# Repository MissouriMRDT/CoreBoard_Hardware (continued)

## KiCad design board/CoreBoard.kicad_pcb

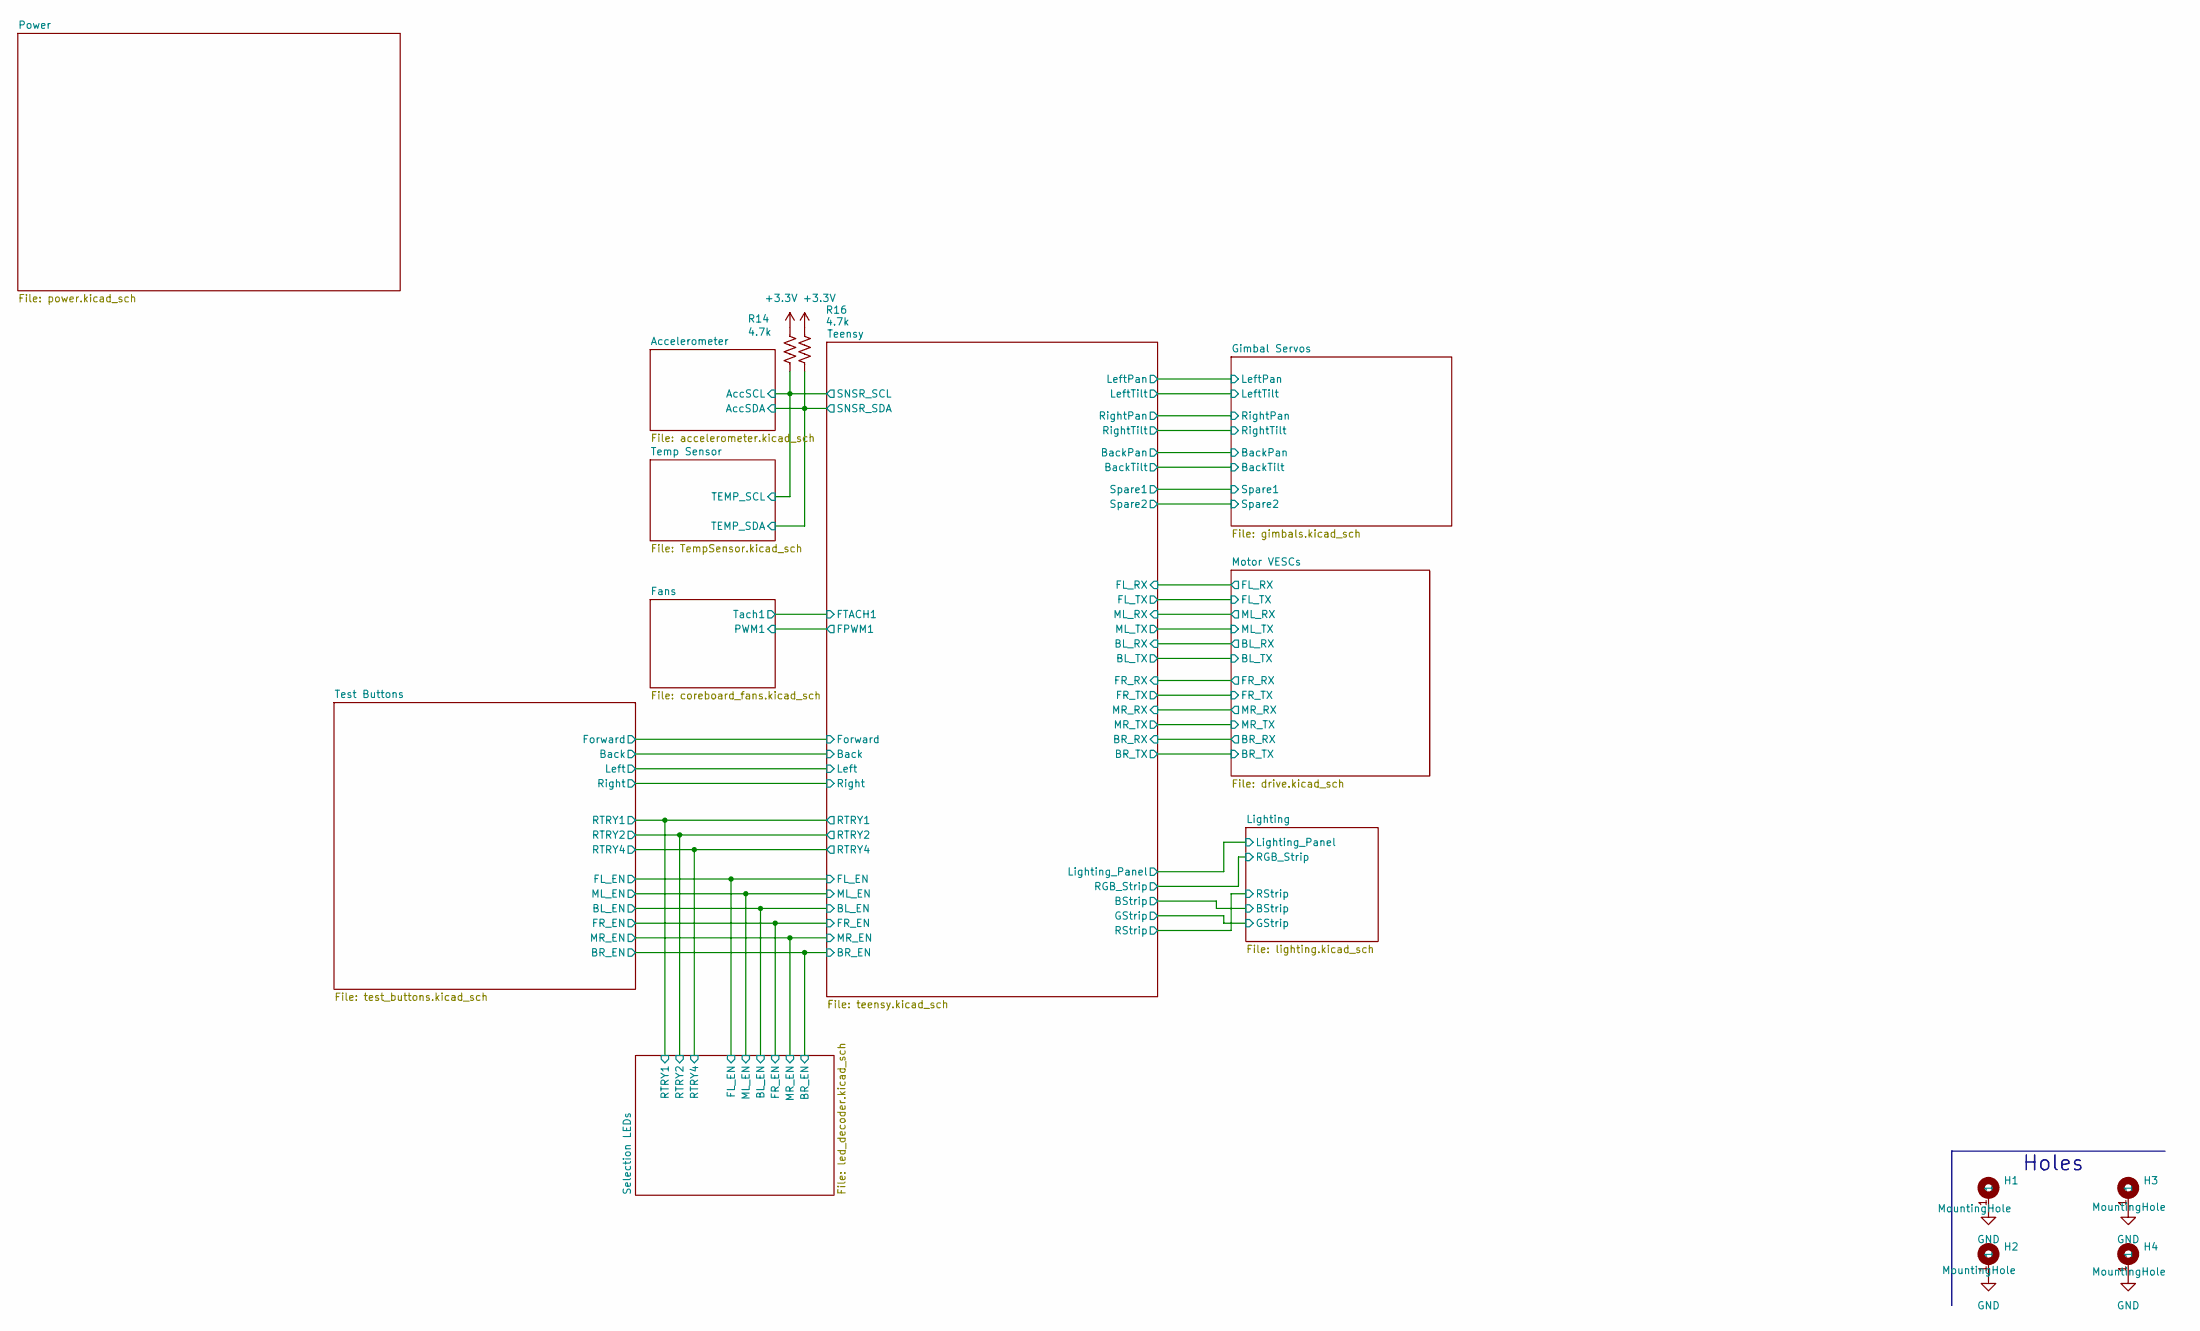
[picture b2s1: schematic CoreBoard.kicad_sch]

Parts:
H1, H2, H3, H4: MountingHole; 4_40_Hole_Pad_Via
R14, R16: 4.7k; R_0603_1608Metric_Pad0.98x0.95mm_HandSolder

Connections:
+3.3V: R14.1, R16.1; also elsewhere on the board
/Accelerometer/AccSCL: R14.2; also elsewhere on the board
/Accelerometer/AccSDA: R16.2; also elsewhere on the board
GND: H1.1, H2.1, H3.1, H4.1; also elsewhere on the board

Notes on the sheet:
Holes

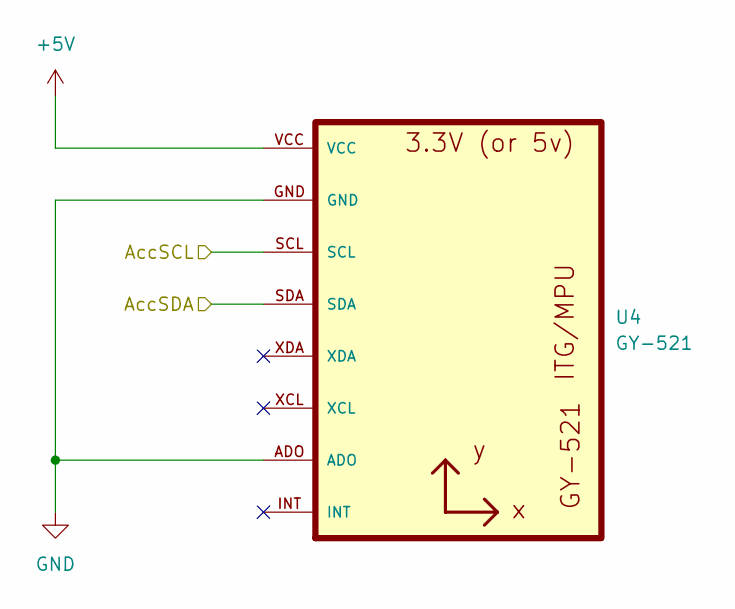
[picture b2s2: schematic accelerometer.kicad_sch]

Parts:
U4: GY-521

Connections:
+5V: U4.VCC; also elsewhere on the board
/Accelerometer/AccSCL: U4.SCL; also elsewhere on the board
/Accelerometer/AccSDA: U4.SDA; also elsewhere on the board
GND: U4.ADO, U4.GND; also elsewhere on the board

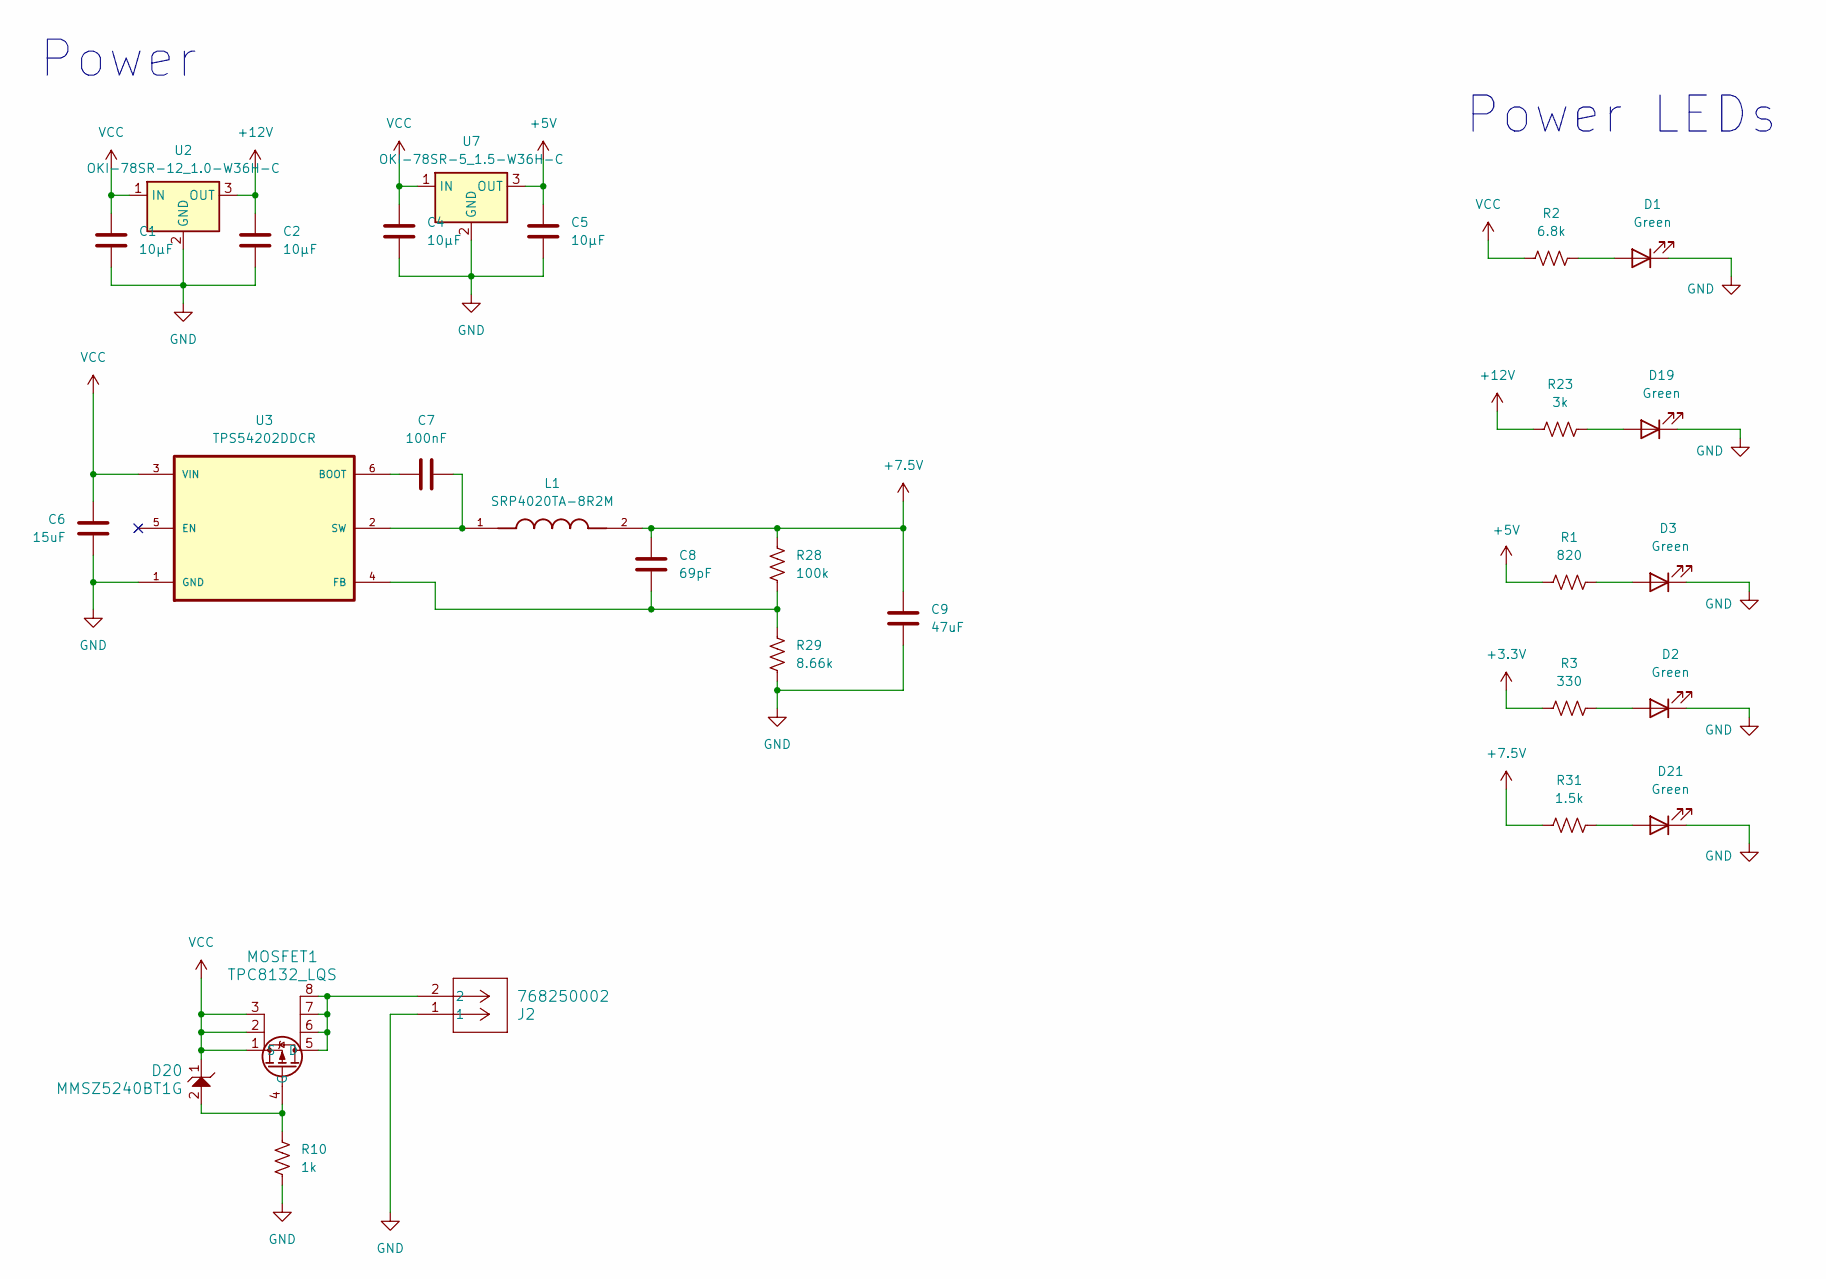
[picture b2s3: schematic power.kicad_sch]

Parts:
C1, C4: 10µF; C_1206_3216Metric_Pad1.33x1.80mm_HandSolder
C2, C5: 10µF; C_0603_1608Metric_Pad1.08x0.95mm_HandSolder
C6: 15uF; C_0805_2012Metric_Pad1.18x1.45mm_HandSolder
C7: 100nF; C_0603_1608Metric
C8: 69pF; C_0603_1608Metric
C9: 47uF; C_1206_3216Metric
D1, D2, D3, D19, D21: Green; LED_0603_1608Metric_Pad1.05x0.95mm_HandSolder
D20: MMSZ5240BT1G; SOD-123_ONS-L
J2: 768250002; MOLEX_MegaFit_02_Horizontal
L1: SRP4020TA-8R2M; IND_SRP4020TA-8R2M
MOSFET1: TPC8132_LQS; SOIC-8_3.9x4.9mm_P1.27mm
R1: 820; R_0603_1608Metric_Pad0.98x0.95mm_HandSolder
R2: 6.8k; R_0603_1608Metric_Pad0.98x0.95mm_HandSolder
R3: 330; R_0603_1608Metric_Pad0.98x0.95mm_HandSolder
R10: 1k; R_0603_1608Metric_Pad0.98x0.95mm_HandSolder
R23: 3k; R_0603_1608Metric_Pad0.98x0.95mm_HandSolder
R28: 100k; R_0603_1608Metric
R29: 8.66k; R_0603_1608Metric
R31: 1.5k; R_0603_1608Metric_Pad0.98x0.95mm_HandSolder
U2: OKI-78SR-12_1.0-W36H-C; Converter_DCDC_Murata_OKI-78SR_Horizontal
U3: TPS54202DDCR; SOT95P280X110-6N; MPN TPS54202DDCR
U7: OKI-78SR-5_1.5-W36H-C; Converter_DCDC_Murata_OKI-78SR_Horizontal

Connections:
+3.3V: R3.1; also elsewhere on the board
+5V: C5.1, R1.1, U7.3 (OUT); also elsewhere on the board
+7.5V: C8.1, C9.1, L1.2, R28.1, R31.1; also elsewhere on the board
+12V: C2.1, R23.1, U2.3 (OUT); also elsewhere on the board
GND: C1.2, C2.2, C4.2, C5.2, C6.2, C9.2, D1.1 (K), D2.1 (K), D3.1 (K), D19.1 (K), D21.1 (K), J2.1, R10.1, R29.2, U2.2 (GND), U3.1 (GND), U7.2 (GND); also elsewhere on the board
unnamed: D1.2 (A), R2.2
unnamed: D2.2 (A), R3.2
unnamed: D3.2 (A), R1.2
unnamed: D19.2 (A), R23.2
unnamed: D21.2 (A), R31.2
unnamed: J2.2, MOSFET1.5 (D), MOSFET1.6, MOSFET1.7, MOSFET1.8
unnamed: D20.2, MOSFET1.4 (G), R10.2
unnamed: C7.1, U3.6 (BOOT)
unnamed: C8.2, R28.2, R29.1, U3.4 (FB)
unnamed: C7.2, L1.1, U3.2 (SW)
VCC: C1.1, C4.1, C6.1, D20.1, MOSFET1.1 (S), MOSFET1.2, MOSFET1.3, R2.1, U2.1 (IN), U3.3 (VIN), U7.1 (IN)

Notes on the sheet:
Power
Power LEDs

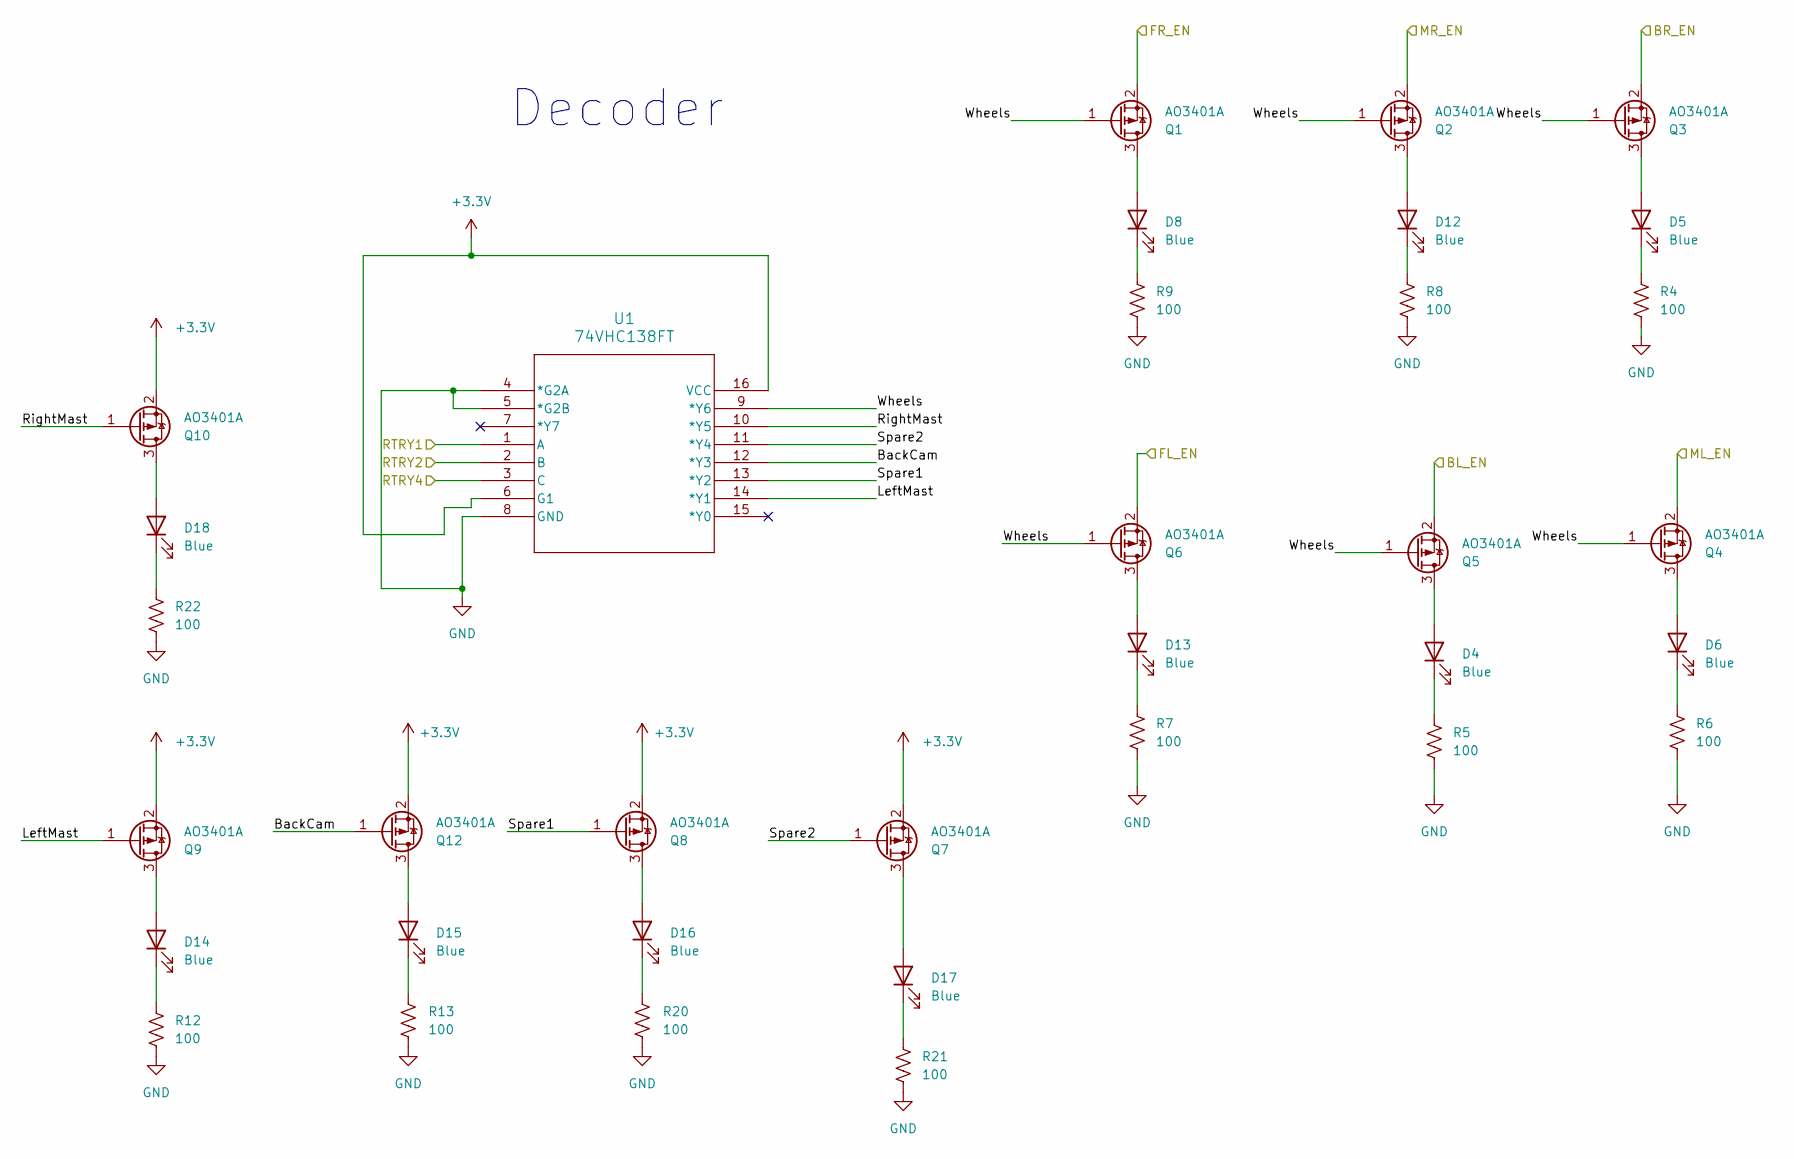
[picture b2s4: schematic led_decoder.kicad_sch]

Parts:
D4, D5, D6, D8, D12, D13, D14, D15, D16, D17, D18: Blue; LED_0603_1608Metric_Pad1.05x0.95mm_HandSolder
Q1, Q2, Q3, Q4, Q5, Q6, Q7, Q8, Q9, Q10, Q12: AO3401A; SOT-23
R4, R5, R6, R7, R8, R9, R12, R13, R20, R21, R22: 100; R_0603_1608Metric_Pad0.98x0.95mm_HandSolder
U1: 74VHC138FT; TSSOP16B_TOS-L

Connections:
+3.3V: Q7.2 (S), Q8.2 (S), Q9.2 (S), Q10.2 (S), Q12.2 (S), U1.6 (G1), U1.16 (VCC); also elsewhere on the board
/Selection LEDs/BL_EN: Q5.2 (S); also elsewhere on the board
/Selection LEDs/BR_EN: Q3.2 (S); also elsewhere on the board
/Selection LEDs/BackCam: Q12.1 (G), U1.12 (*Y3)
/Selection LEDs/FL_EN: Q6.2 (S); also elsewhere on the board
/Selection LEDs/FR_EN: Q1.2 (S); also elsewhere on the board
/Selection LEDs/LeftMast: Q9.1 (G), U1.14 (*Y1)
/Selection LEDs/ML_EN: Q4.2 (S); also elsewhere on the board
/Selection LEDs/MR_EN: Q2.2 (S); also elsewhere on the board
/Selection LEDs/RTRY1: U1.1 (A); also elsewhere on the board
/Selection LEDs/RTRY2: U1.2 (B); also elsewhere on the board
/Selection LEDs/RTRY4: U1.3 (C); also elsewhere on the board
/Selection LEDs/RightMast: Q10.1 (G), U1.10 (*Y5)
/Selection LEDs/Spare1: Q8.1 (G), U1.13 (*Y2)
/Selection LEDs/Spare2: Q7.1 (G), U1.11 (*Y4)
/Selection LEDs/Wheels: Q1.1 (G), Q2.1 (G), Q3.1 (G), Q4.1 (G), Q5.1 (G), Q6.1 (G), U1.9 (*Y6)
GND: R4.1, R5.1, R6.1, R7.1, R8.1, R9.1, R12.1, R13.1, R20.1, R21.1, R22.1, U1.4 (*G2A), U1.5 (*G2B), U1.8 (GND); also elsewhere on the board
unnamed: D4.2 (A), Q5.3 (D)
unnamed: D4.1 (K), R5.2
unnamed: D5.2 (A), Q3.3 (D)
unnamed: D5.1 (K), R4.2
unnamed: D6.2 (A), Q4.3 (D)
unnamed: D6.1 (K), R6.2
unnamed: D8.2 (A), Q1.3 (D)
unnamed: D8.1 (K), R9.2
unnamed: D12.2 (A), Q2.3 (D)
unnamed: D12.1 (K), R8.2
unnamed: D13.2 (A), Q6.3 (D)
unnamed: D13.1 (K), R7.2
unnamed: D14.2 (A), Q9.3 (D)
unnamed: D14.1 (K), R12.2
unnamed: D15.2 (A), Q12.3 (D)
unnamed: D15.1 (K), R13.2
unnamed: D16.2 (A), Q8.3 (D)
unnamed: D16.1 (K), R20.2
unnamed: D17.2 (A), Q7.3 (D)
unnamed: D17.1 (K), R21.2
unnamed: D18.2 (A), Q10.3 (D)
unnamed: D18.1 (K), R22.2

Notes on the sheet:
Decoder

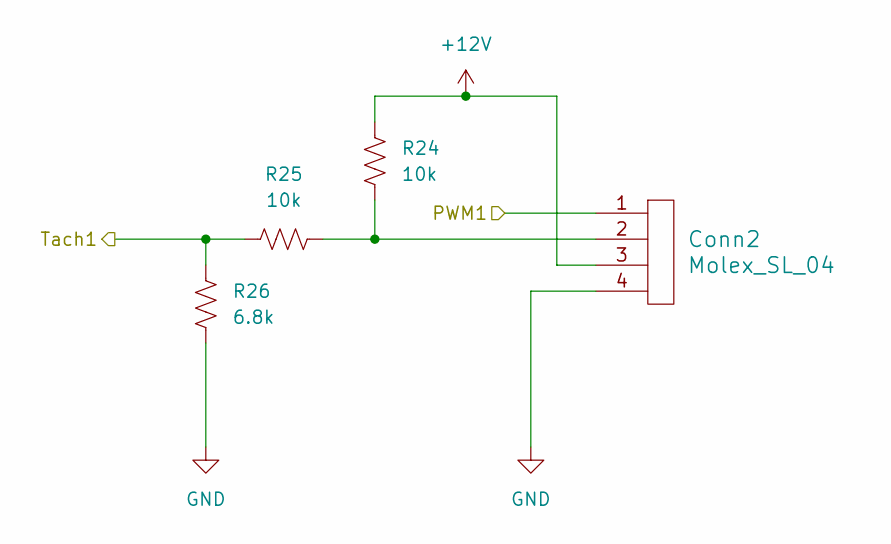
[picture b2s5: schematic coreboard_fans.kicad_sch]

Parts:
Conn2: Molex_SL_04; MOLEX_SL_04_Horizontal
R24, R25: 10k; R_0603_1608Metric_Pad0.98x0.95mm_HandSolder
R26: 6.8k; R_0603_1608Metric_Pad0.98x0.95mm_HandSolder

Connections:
+12V: Conn2.3, R24.1; also elsewhere on the board
/Fans/PWM1: Conn2.1; also elsewhere on the board
/Fans/Tach1: R25.2, R26.1; also elsewhere on the board
GND: Conn2.4, R26.2; also elsewhere on the board
unnamed: Conn2.2, R24.2, R25.1

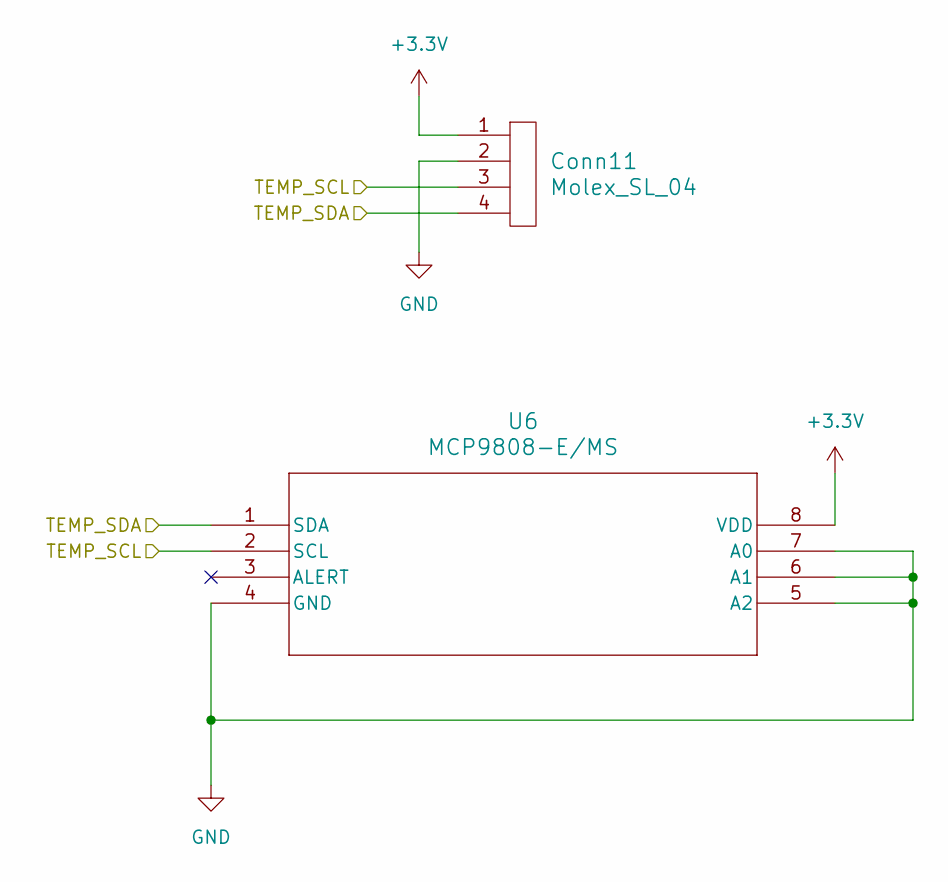
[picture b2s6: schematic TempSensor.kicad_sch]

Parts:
Conn11: Molex_SL_04; MOLEX_SL_04_Vertical
U6: MCP9808-E/MS; MSOP8_MC_MCH-L

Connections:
+3.3V: Conn11.1, U6.8 (VDD); also elsewhere on the board
/Accelerometer/AccSCL: Conn11.3, U6.2 (SCL); also elsewhere on the board
/Accelerometer/AccSDA: Conn11.4, U6.1 (SDA); also elsewhere on the board
GND: Conn11.2, U6.4 (GND), U6.5 (A2), U6.6 (A1), U6.7 (A0); also elsewhere on the board

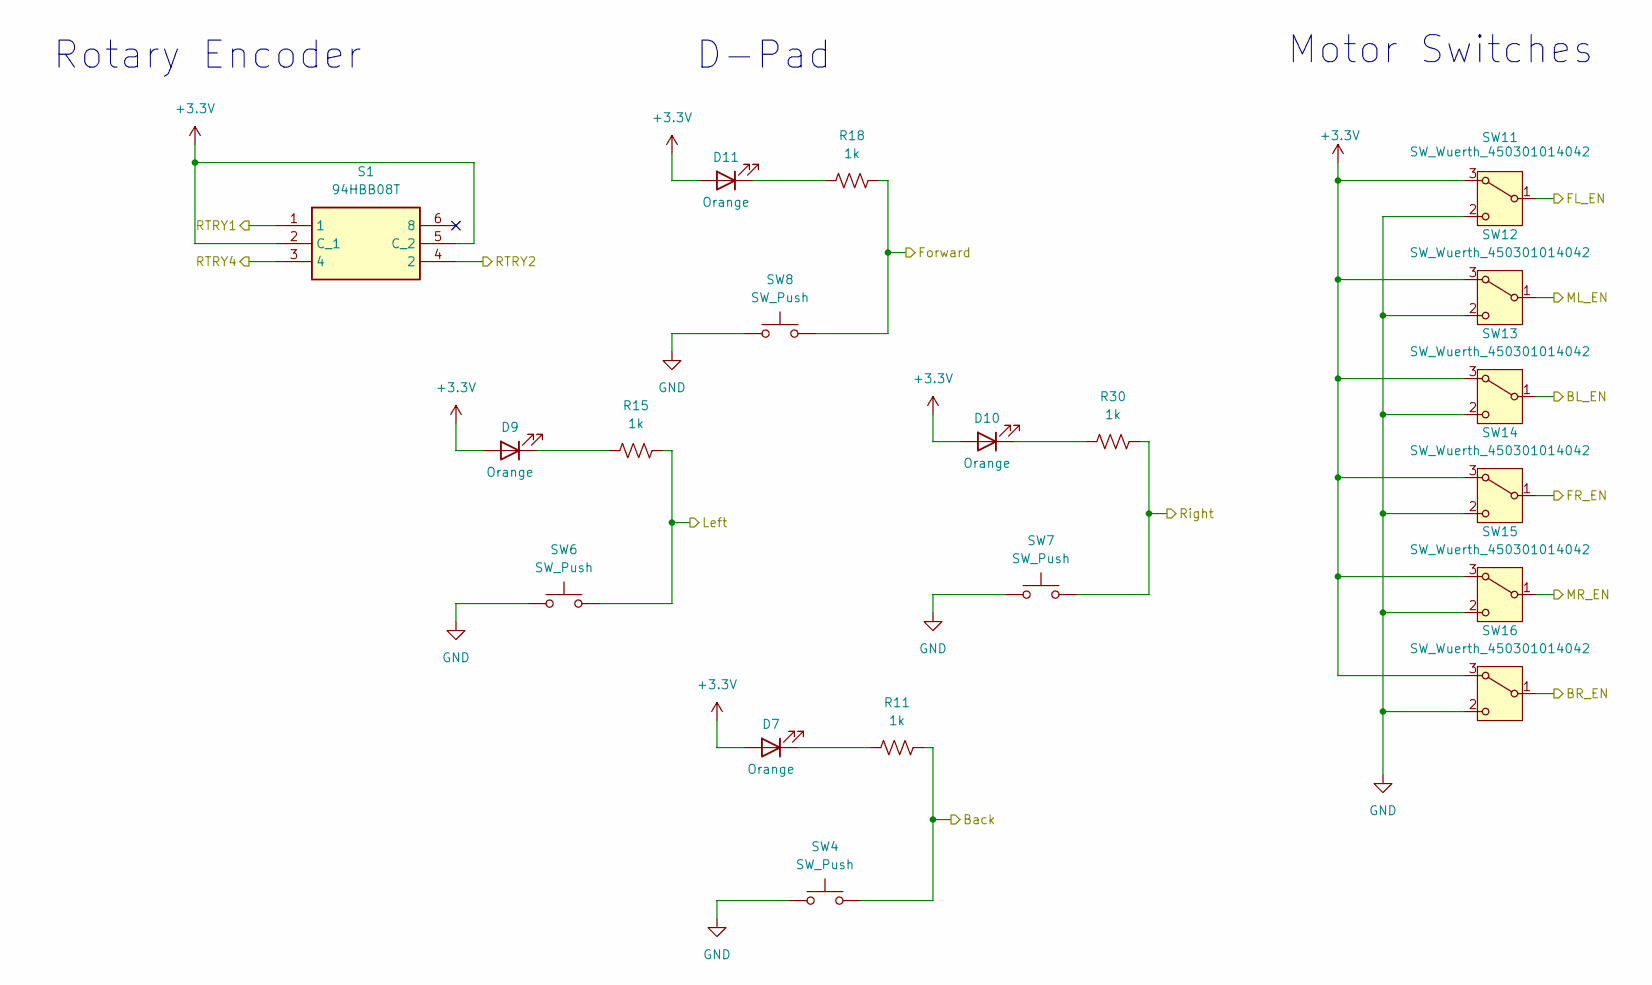
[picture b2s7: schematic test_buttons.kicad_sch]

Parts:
D7, D9, D10, D11: Orange; LED_0603_1608Metric_Pad1.05x0.95mm_HandSolder
R11, R15, R18, R30: 1k; R_0603_1608Metric_Pad0.98x0.95mm_HandSolder
S1: 94HBB08T; DIPS762W56P254L991H597Q6N; Manufacturer_Part_Number 94HBB08T; Mouser Part Number 706-94HBB08T
SW4, SW6, SW7, SW8: SW_Push; SW_SPST_TL3305A
SW11, SW12, SW13, SW14, SW15, SW16: SW_Wuerth_450301014042; SW_Slide-03_Wuerth-WS-SLTV_10x2.5x6.4_P2.54mm

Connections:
+3.3V: D7.2 (A), D9.2 (A), D10.2 (A), D11.2 (A), S1.2 (C_1), S1.5 (C_2), SW11.3 (A), SW12.3 (A), SW13.3 (A), SW14.3 (A), SW15.3 (A), SW16.3 (A); also elsewhere on the board
/Selection LEDs/BL_EN: SW13.1 (B); also elsewhere on the board
/Selection LEDs/BR_EN: SW16.1 (B); also elsewhere on the board
/Selection LEDs/FL_EN: SW11.1 (B); also elsewhere on the board
/Selection LEDs/FR_EN: SW14.1 (B); also elsewhere on the board
/Selection LEDs/ML_EN: SW12.1 (B); also elsewhere on the board
/Selection LEDs/MR_EN: SW15.1 (B); also elsewhere on the board
/Selection LEDs/RTRY1: S1.1; also elsewhere on the board
/Selection LEDs/RTRY2: S1.4 (2); also elsewhere on the board
/Selection LEDs/RTRY4: S1.3 (4); also elsewhere on the board
/Teensy/Back: R11.1, SW4.2; also elsewhere on the board
/Teensy/Forward: R18.1, SW8.2; also elsewhere on the board
/Teensy/Left: R15.1, SW6.2; also elsewhere on the board
/Teensy/Right: R30.1, SW7.2; also elsewhere on the board
GND: SW4.1, SW6.1, SW7.1, SW8.1, SW11.2 (C), SW12.2 (C), SW13.2 (C), SW14.2 (C), SW15.2 (C), SW16.2 (C); also elsewhere on the board
unnamed: D7.1 (K), R11.2
unnamed: D9.1 (K), R15.2
unnamed: D10.1 (K), R30.2
unnamed: D11.1 (K), R18.2

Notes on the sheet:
Motor Switches
Rotary Encoder
D-Pad

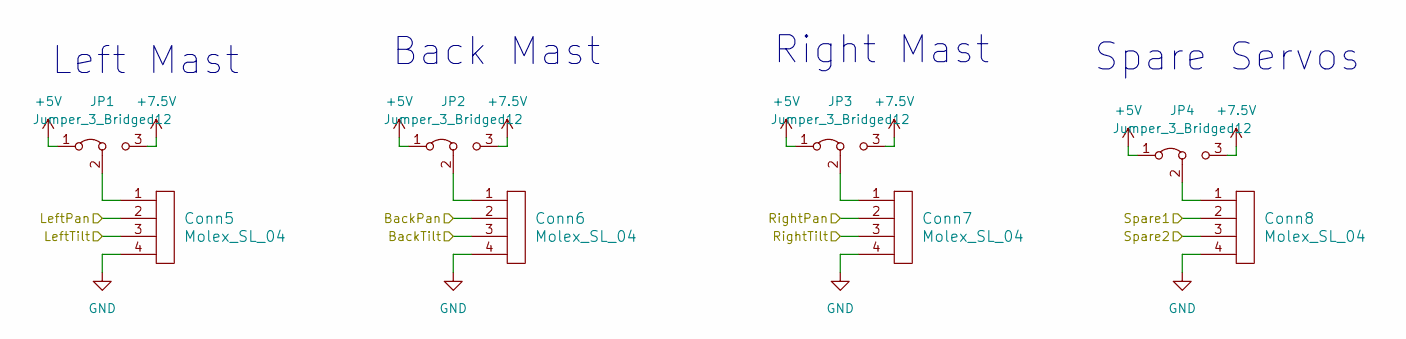
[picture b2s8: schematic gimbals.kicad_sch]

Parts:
Conn5, Conn6, Conn7, Conn8: Molex_SL_04; MOLEX_SL_04_Vertical
JP1, JP2, JP3, JP4: Jumper_3_Bridged12; PinHeader_1x03_P2.54mm_Vertical

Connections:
+5V: JP1.1 (A), JP2.1 (A), JP3.1 (A), JP4.1 (A); also elsewhere on the board
+7.5V: JP1.3 (B), JP2.3 (B), JP3.3 (B), JP4.3 (B); also elsewhere on the board
/Gimbal Servos/BackPan: Conn6.2; also elsewhere on the board
/Gimbal Servos/BackTilt: Conn6.3; also elsewhere on the board
/Gimbal Servos/LeftPan: Conn5.2; also elsewhere on the board
/Gimbal Servos/LeftTilt: Conn5.3; also elsewhere on the board
/Gimbal Servos/RightPan: Conn7.2; also elsewhere on the board
/Gimbal Servos/RightTilt: Conn7.3; also elsewhere on the board
/Gimbal Servos/Spare1: Conn8.2; also elsewhere on the board
/Gimbal Servos/Spare2: Conn8.3; also elsewhere on the board
GND: Conn5.4, Conn6.4, Conn7.4, Conn8.4; also elsewhere on the board
unnamed: Conn5.1, JP1.2 (C)
unnamed: Conn6.1, JP2.2 (C)
unnamed: Conn7.1, JP3.2 (C)
unnamed: Conn8.1, JP4.2 (C)

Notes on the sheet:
Back Mast
Right Mast
Left Mast
Spare Servos

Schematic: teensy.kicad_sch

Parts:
C3: 0.1µF; C_0603_1608Metric_Pad1.08x0.95mm_HandSolder
J1: RJ45_LED_Shielded; RJ45_Teensy
U5: Teensy4.1_DEV-16771; Teensy_4_1_Ethernet; PARTREV 4.1

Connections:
+3.3V: U5.3.3V_1 (3.3V), U5.3.3V_2 (3.3V), U5.3.3V_3 (3.3V); also elsewhere on the board
+5V: U5.5V, U5.VIN; also elsewhere on the board
/Accelerometer/AccSCL: U5.19 (A5); also elsewhere on the board
/Accelerometer/AccSDA: U5.18 (A4); also elsewhere on the board
/Fans/PWM1: U5.10 (CS1); also elsewhere on the board
/Fans/Tach1: U5.3 (LRCLK2); also elsewhere on the board
/Gimbal Servos/BackPan: U5.12 (MISO); also elsewhere on the board
/Gimbal Servos/BackTilt: U5.11 (MOSI); also elsewhere on the board
/Gimbal Servos/LeftPan: U5.7 (RX2); also elsewhere on the board
/Gimbal Servos/LeftTilt: U5.8 (TX2); also elsewhere on the board
/Gimbal Servos/RightPan: U5.2 (OUT2); also elsewhere on the board
/Gimbal Servos/RightTilt: U5.6 (OUT1D); also elsewhere on the board
/Gimbal Servos/Spare1: U5.22 (A8); also elsewhere on the board
/Gimbal Servos/Spare2: U5.5 (IN2); also elsewhere on the board
/Lighting/BStrip: U5.9 (OUT1C); also elsewhere on the board
/Lighting/GStrip: U5.33 (MCLK2); also elsewhere on the board
/Lighting/Lighting_Panel: U5.17 (A3); also elsewhere on the board
/Lighting/RGB_Strip: U5.16 (A2); also elsewhere on the board
/Lighting/RStrip: U5.4 (BCLK2); also elsewhere on the board
/Motor VESCs/BL_RX: U5.21 (A7); also elsewhere on the board
/Motor VESCs/BL_TX: U5.20 (A6); also elsewhere on the board
/Motor VESCs/BR_RX: U5.0 (RX1); also elsewhere on the board
/Motor VESCs/BR_TX: U5.1 (TX1); also elsewhere on the board
/Motor VESCs/FL_RX: U5.34 (RX8); also elsewhere on the board
/Motor VESCs/FL_TX: U5.35 (TX8); also elsewhere on the board
/Motor VESCs/FR_RX: U5.28 (RX7); also elsewhere on the board
/Motor VESCs/FR_TX: U5.29 (TX7); also elsewhere on the board
/Motor VESCs/ML_RX: U5.15 (A1); also elsewhere on the board
/Motor VESCs/ML_TX: U5.14 (A0); also elsewhere on the board
/Motor VESCs/MR_RX: U5.25 (A11); also elsewhere on the board
/Motor VESCs/MR_TX: U5.24 (A10); also elsewhere on the board
/Selection LEDs/BL_EN: U5.38 (A14); also elsewhere on the board
/Selection LEDs/BR_EN: U5.41 (A17); also elsewhere on the board
/Selection LEDs/FL_EN: U5.36 (CS2); also elsewhere on the board
/Selection LEDs/FR_EN: U5.39 (A15); also elsewhere on the board
/Selection LEDs/ML_EN: U5.37 (CS3); also elsewhere on the board
/Selection LEDs/MR_EN: U5.40 (A16); also elsewhere on the board
/Selection LEDs/RTRY1: U5.26 (A12); also elsewhere on the board
/Selection LEDs/RTRY2: U5.30 (CRX3); also elsewhere on the board
/Selection LEDs/RTRY4: U5.31 (CTX3); also elsewhere on the board
/Teensy/Back: U5.13 (SCK); also elsewhere on the board
/Teensy/Forward: U5.32 (OUT1B); also elsewhere on the board
/Teensy/Left: U5.27 (A13); also elsewhere on the board
/Teensy/Right: U5.23 (A9); also elsewhere on the board
GND: C3.2, J1.8, J1.9, J1.SH, U5.GND1 (GND), U5.GND2 (GND), U5.GND3 (GND), U5.GND4 (GND), U5.GND5 (GND), U5.USB_GND1 (USB_GND), U5.USB_GND2 (USB_GND); also elsewhere on the board
LED: J1.10, U5.LED
unnamed: C3.1, J1.2, J1.5
Rx+: J1.4, U5.R+
Rx-: J1.6, U5.R-
Tx+: J1.1, U5.T+
Tx-: J1.3, U5.T-

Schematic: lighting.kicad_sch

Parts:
Conn1, Conn10: Molex_SL_03; MOLEX_SL_03_Horizontal
Conn9: Molex_SL_04; MOLEX_SL_04_Horizontal
Q16, Q17, Q18: BSS138; SOT-23
R17, R19, R27: 10k; R_0603_1608Metric_Pad0.98x0.95mm_HandSolder

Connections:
+5V: Conn1.1, Conn9.1, Conn10.1; also elsewhere on the board
/Lighting/BStrip: Q18.1 (G), R27.1; also elsewhere on the board
/Lighting/GStrip: Q17.1 (G), R19.1; also elsewhere on the board
/Lighting/Lighting_Panel: Conn10.2; also elsewhere on the board
/Lighting/RGB_Strip: Conn1.2; also elsewhere on the board
/Lighting/RStrip: Q16.1 (G), R17.1; also elsewhere on the board
GND: Conn1.3, Conn10.3, Q16.2 (S), Q17.2 (S), Q18.2 (S), R17.2, R19.2, R27.2; also elsewhere on the board
unnamed: Conn9.4, Q16.3 (D)
unnamed: Conn9.3, Q17.3 (D)
unnamed: Conn9.2, Q18.3 (D)

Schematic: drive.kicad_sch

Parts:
Conn3, Conn4: Molex_SL_09; MOLEX_SL_09_Horizontal

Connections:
/Motor VESCs/BL_RX: Conn3.2; also elsewhere on the board
/Motor VESCs/BL_TX: Conn3.1; also elsewhere on the board
/Motor VESCs/BR_RX: Conn4.8; also elsewhere on the board
/Motor VESCs/BR_TX: Conn4.9; also elsewhere on the board
/Motor VESCs/FL_RX: Conn3.8; also elsewhere on the board
/Motor VESCs/FL_TX: Conn3.7; also elsewhere on the board
/Motor VESCs/FR_RX: Conn4.2; also elsewhere on the board
/Motor VESCs/FR_TX: Conn4.3; also elsewhere on the board
/Motor VESCs/ML_RX: Conn3.5; also elsewhere on the board
/Motor VESCs/ML_TX: Conn3.4; also elsewhere on the board
/Motor VESCs/MR_RX: Conn4.5; also elsewhere on the board
/Motor VESCs/MR_TX: Conn4.6; also elsewhere on the board
GND: Conn3.3, Conn3.6, Conn3.9, Conn4.1, Conn4.4, Conn4.7; also elsewhere on the board

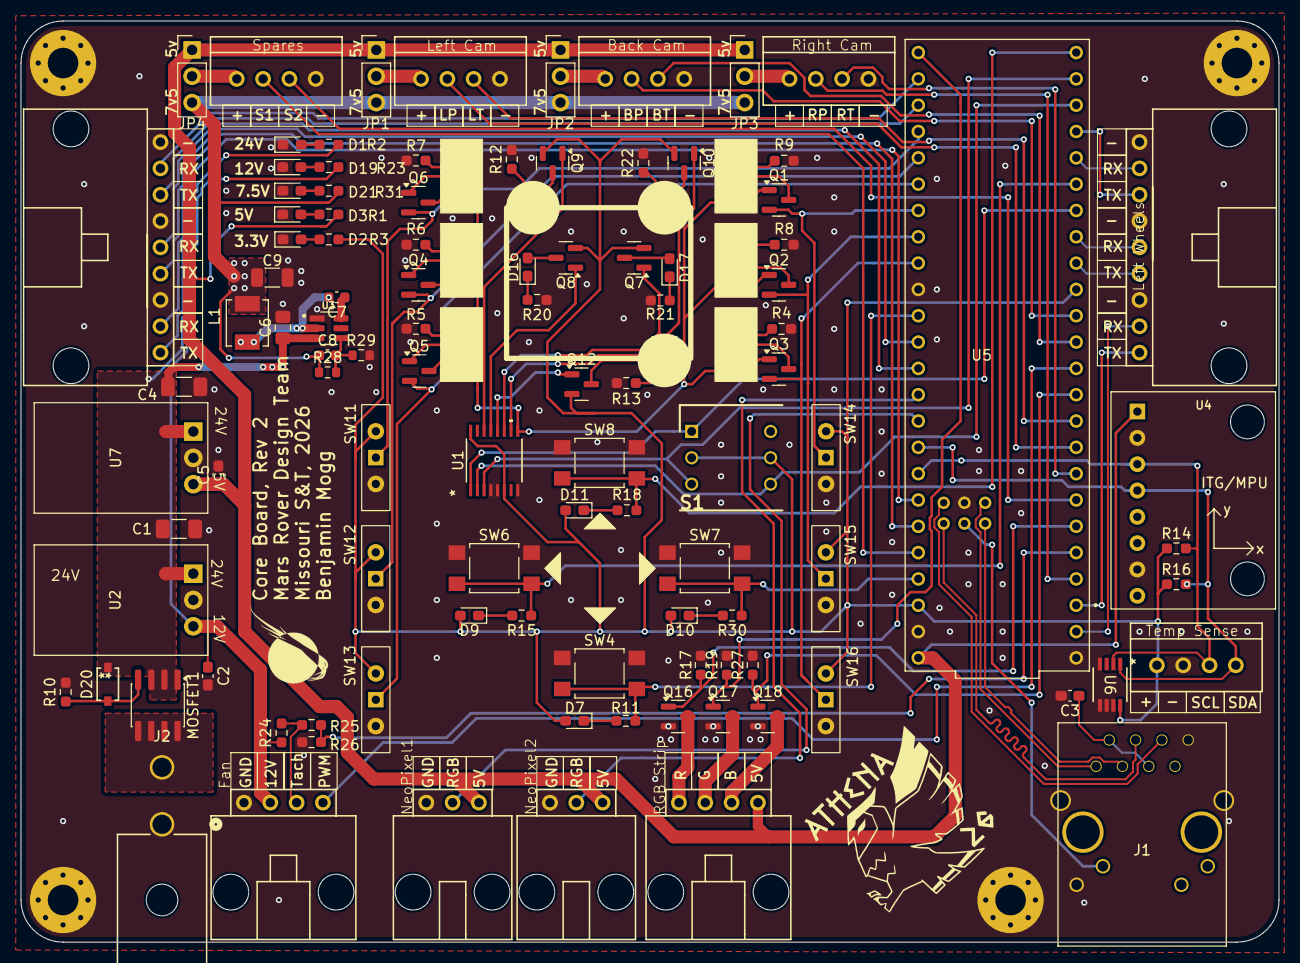
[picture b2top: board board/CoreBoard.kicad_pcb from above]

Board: 2 copper layers, 121.4 x 88.9 mm, 116 parts (0 on the bottom side), 104 nets.
